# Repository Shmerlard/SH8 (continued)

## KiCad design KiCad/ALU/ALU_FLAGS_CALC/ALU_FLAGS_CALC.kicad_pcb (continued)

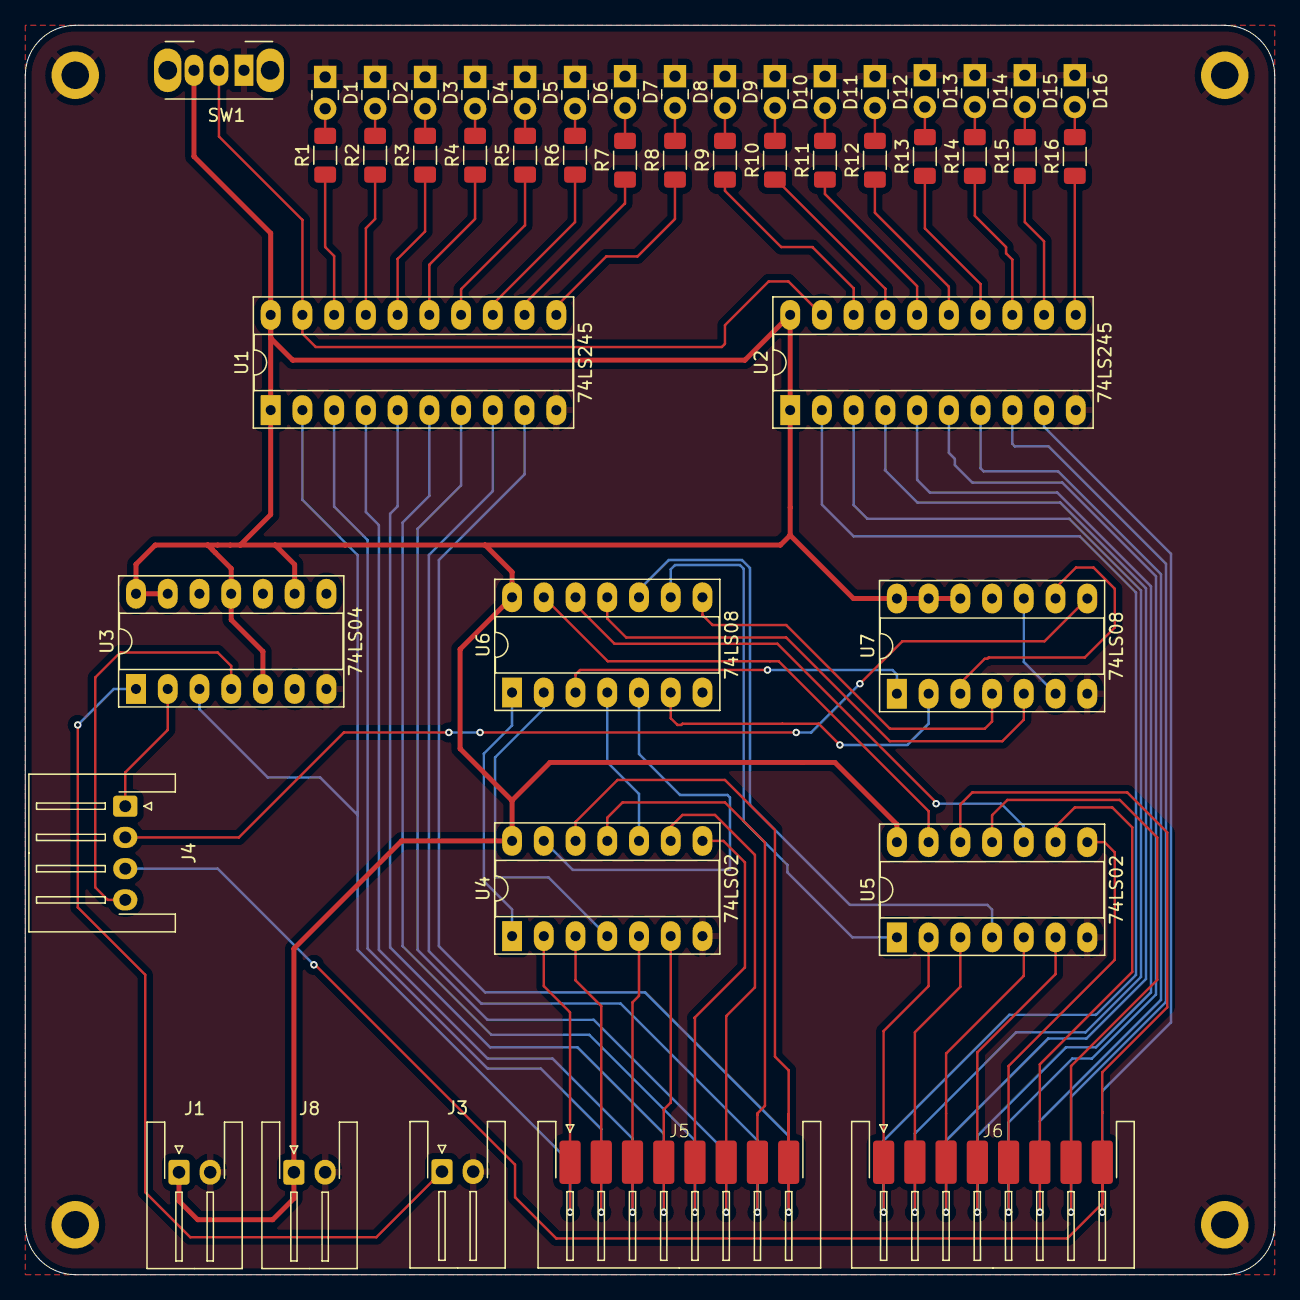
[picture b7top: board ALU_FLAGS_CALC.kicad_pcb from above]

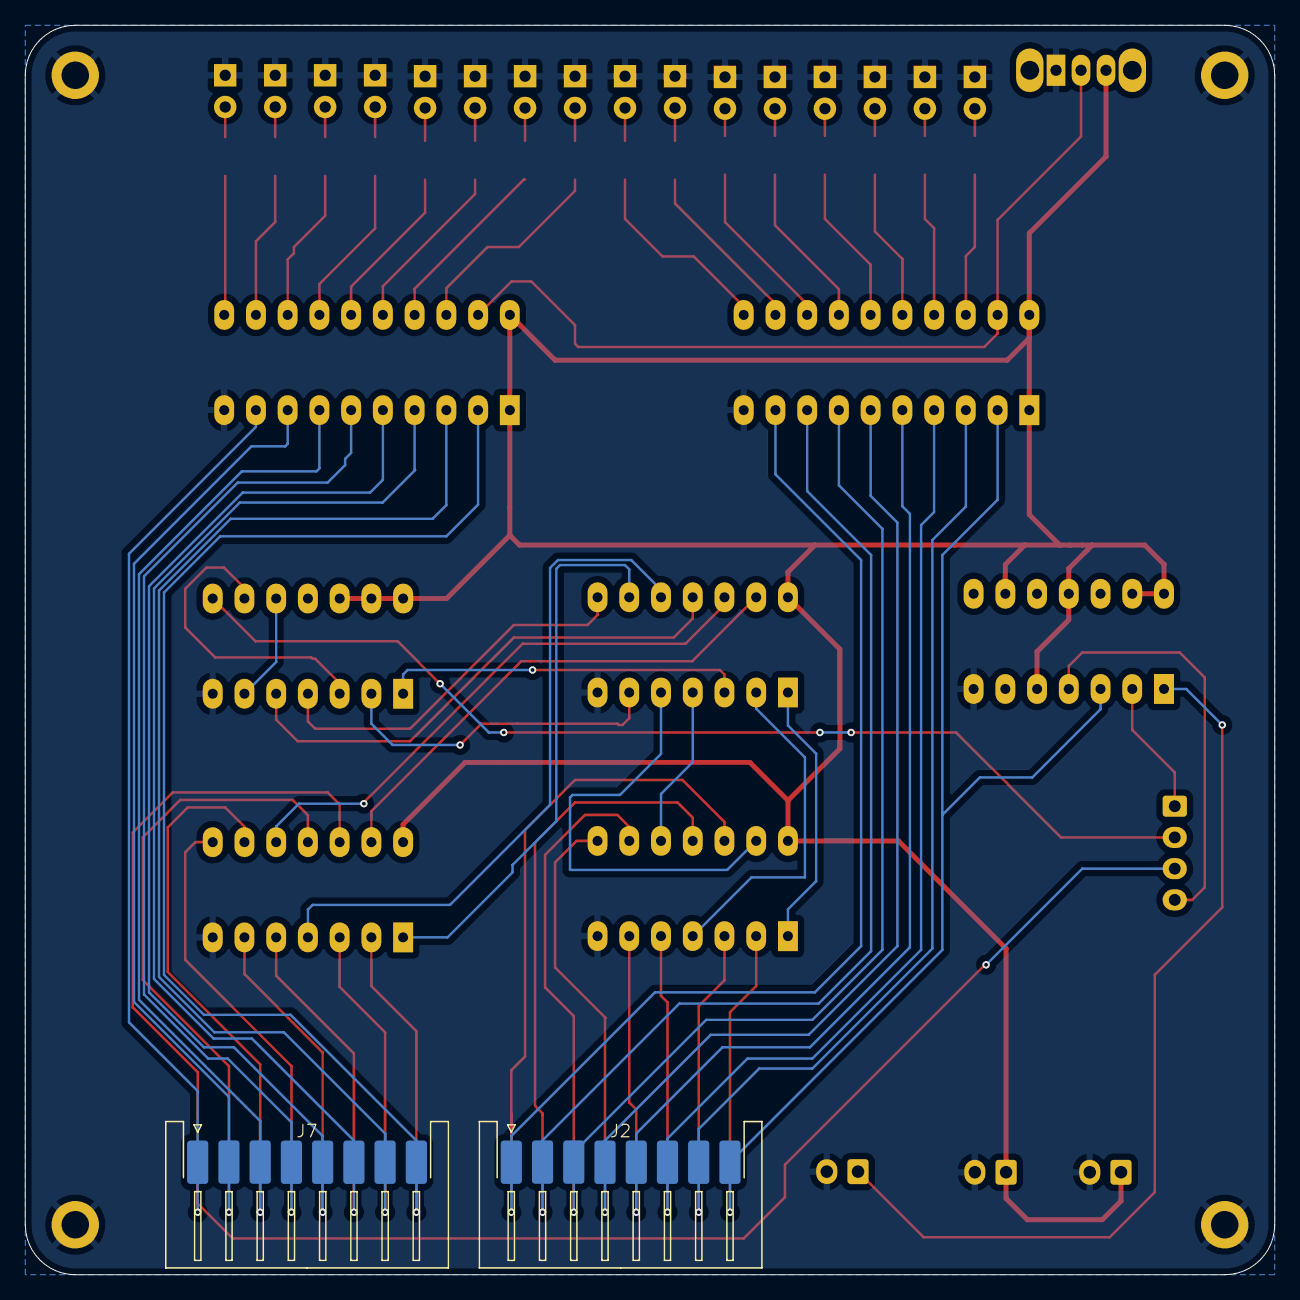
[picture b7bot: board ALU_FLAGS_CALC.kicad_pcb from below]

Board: 2 copper layers, 100.0 x 100.0 mm, 52 parts (2 on the bottom side), 69 nets.

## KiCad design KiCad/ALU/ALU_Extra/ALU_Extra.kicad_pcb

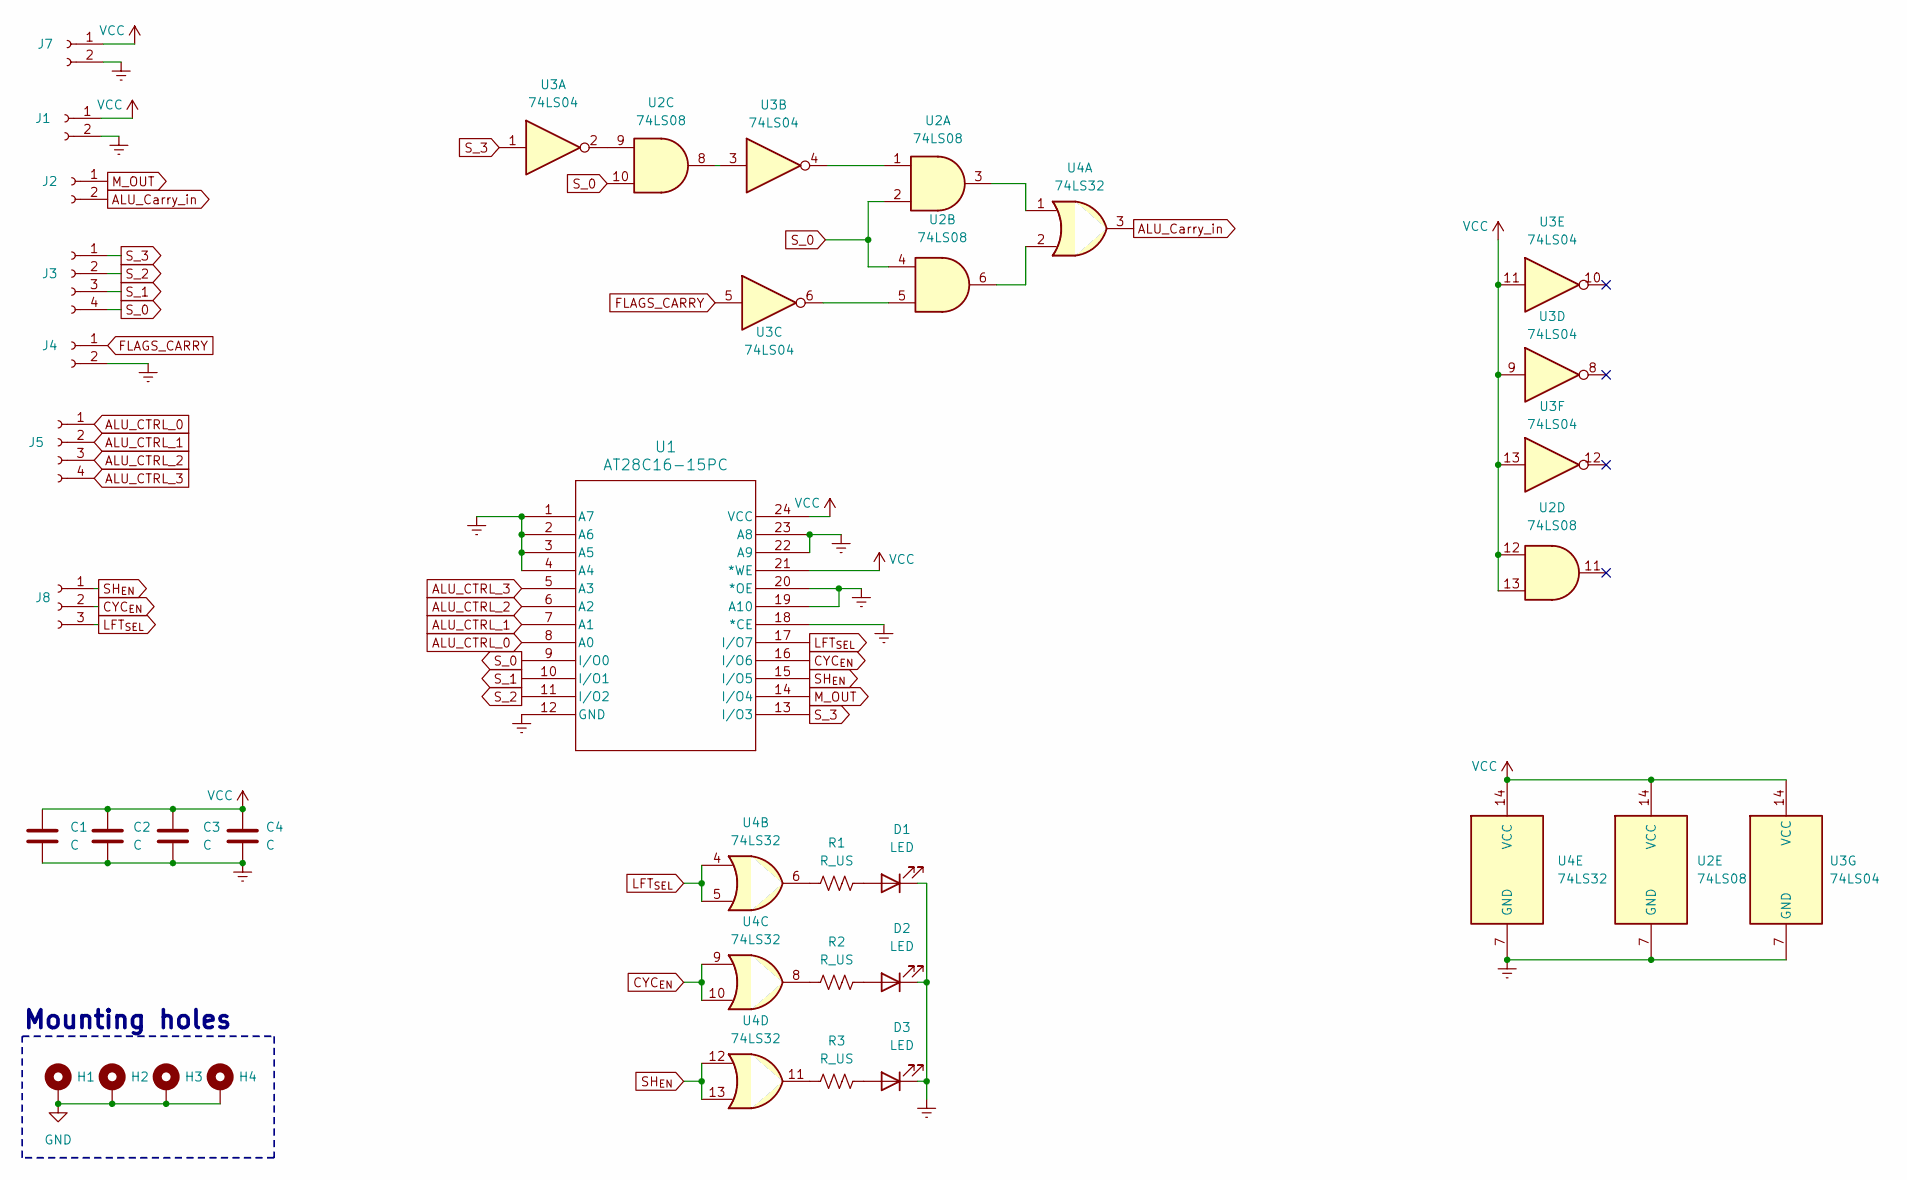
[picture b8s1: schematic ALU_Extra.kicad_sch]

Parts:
C1, C2, C3, C4: C; C_Disc_D3.8mm_W2.6mm_P2.50mm
D1, D2, D3: LED; LED_2512_6332Metric_Pad1.52x3.35mm_HandSolder
H1, H2, H3, H4: MountingHole_Pad; MountingHole_2.2mm_M2_DIN965_Pad
J1, J2, J4, J7: Conn_01x02_Socket; JST_XH_S2B-XH-A-1_1x02_P2.50mm_Horizontal
J3, J5: Conn_01x04_Socket; JST_XH_S4B-XH-A-1_1x04_P2.50mm_Horizontal
J8: Conn_01x03_Socket; JST_XH_S3B-XH-A-1_1x03_P2.50mm_Horizontal
R1, R2, R3: R_US; R_1206_3216Metric_Pad1.30x1.75mm_HandSolder
U1: AT28C16-15PC; DIP-24_W15.24mm_LongPads
U2: 74LS08; DIP-14_W7.62mm_Socket_LongPads
U3: 74LS04; DIP-14_W7.62mm_Socket_LongPads
U4: 74LS32; DIP-14_W7.62mm_Socket_LongPads

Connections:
ALU_CTRL_0: J5.1, U1.8 (A0)
ALU_CTRL_1: J5.2, U1.7 (A1)
ALU_CTRL_2: J5.3, U1.6 (A2)
ALU_CTRL_3: J5.4, U1.5 (A3)
ALU_Carry_in: J2.2, U4.3
CYC_{EN}: J8.2, U1.16 (I/O6), U4.9, U4.10
FLAGS_CARRY: J4.1, U3.5
GND: C1.2, C2.2, C3.2, C4.2, D1.1 (K), D2.1 (K), D3.1 (K), H1.1, H2.1, H3.1, H4.1, J1.2, J4.2, J7.2, U1.1 (A7), U1.2 (A6), U1.3 (A5), U1.4 (A4), U1.12 (GND), U1.18 (*CE), U1.19 (A10), U1.20 (*OE), U1.22 (A9), U1.23 (A8), U2.7 (GND), U3.7 (GND), U4.7 (GND)
LFT_{SEL}: J8.3, U1.17 (I/O7), U4.4, U4.5
M_OUT: J2.1, U1.14 (I/O4)
unnamed: D1.2 (A), R1.2
unnamed: D2.2 (A), R2.2
unnamed: D3.2 (A), R3.2
unnamed: R1.1, U4.6
unnamed: R2.1, U4.8
unnamed: R3.1, U4.11
unnamed: U2.1, U3.4
unnamed: U2.3, U4.1
unnamed: U2.5, U3.6
unnamed: U2.6, U4.2
unnamed: U2.8, U3.3
unnamed: U2.9, U3.2
SH_{EN}: J8.1, U1.15 (I/O5), U4.12, U4.13
S_0: J3.4, U1.9 (I/O0), U2.2, U2.4, U2.10
S_1: J3.3, U1.10 (I/O1)
S_2: J3.2, U1.11 (I/O2)
S_3: J3.1, U1.13 (I/O3), U3.1
VCC: C1.1, C2.1, C3.1, C4.1, J1.1, J7.1, U1.21 (*WE), U1.24 (VCC), U2.12, U2.13, U2.14 (VCC), U3.9, U3.11, U3.13, U3.14 (VCC), U4.14 (VCC)

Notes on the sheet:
Mounting holes

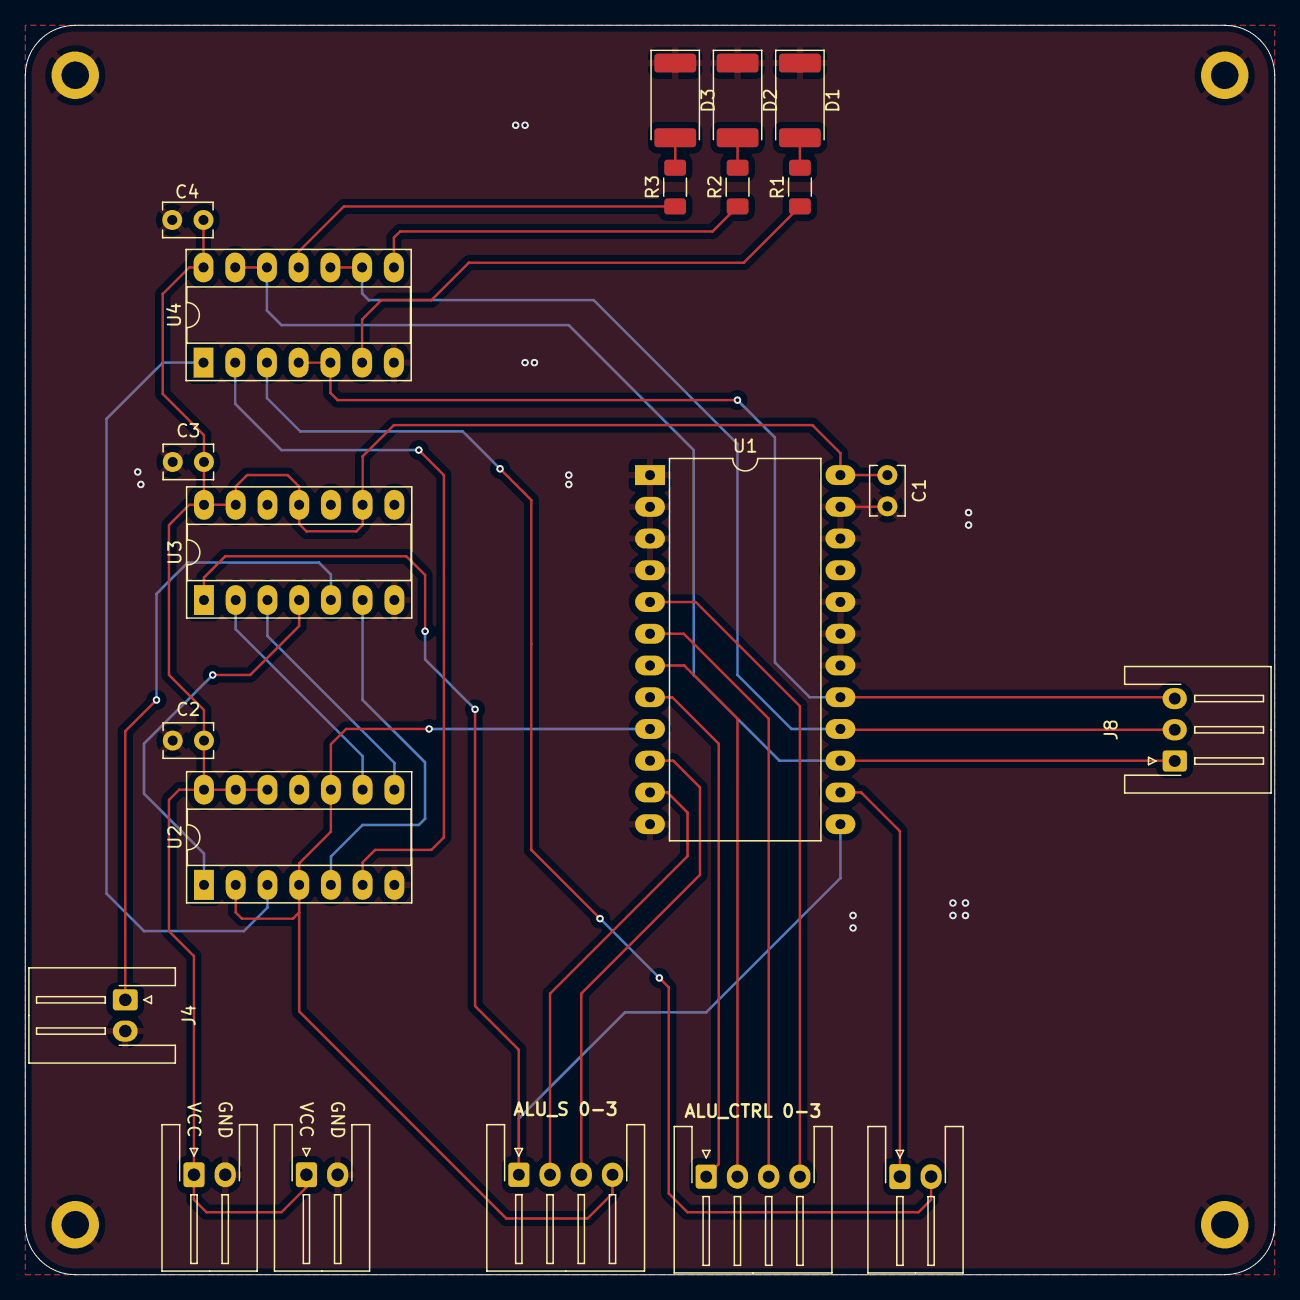
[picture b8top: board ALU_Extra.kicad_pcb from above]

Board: 2 copper layers, 100.0 x 100.0 mm, 25 parts (0 on the bottom side), 28 nets.

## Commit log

2024-06-09 added instruction set
2024-06-09 added circ and diagram
2024-06-09 updated drawing
2024-06-09 added gitignore, updated diagram
2024-06-10 add wiki
2024-06-10 added some to wiki
2024-06-10 modified diagram
    added timing and a few control lines
2024-06-10 background
2024-06-10 changed to 16bit, added logisim
2024-06-10 updated logisim and main diagram
2024-06-10 excel
2024-06-11 added data sheets, and microcode
2024-06-12 addressing modes and instruction format changed
2024-06-12 Added MR, started the assembler,
    updated the instruction format
    added problems
2024-06-13 alu
    added a working alu to logisim, including the 74xx circuit
2024-06-13 solved the alu and conditions problem
    need to reduce the control lines from the address registers to add SHC, SHA
2024-06-14 shifting is working!
2024-06-14 added a bunch of python code
    added control logic, started the program to write to the control logic
2024-06-14 added eeprom programmer
2024-06-15 fixed some python bugs
2024-06-15 rewrote the python code
2024-06-15 solved the logic problem
2024-06-15 added line to gitignore
2024-06-15 rm -r .vscode/
2024-06-15 some cleaning
2024-06-16 minor changes to readme
2024-06-16 added JMP, fixed conditions
2024-06-17 some wiki additions,
    moving to change the instruction structure and instructrure set.
2024-06-18 changed the instruction
    reduced control logic to 3 eeproms, opcode is now 4 bits, added Vout for different jmp conditions, added special addressing mode for different operations
2024-06-21 added control lines description
2024-06-21 added control lines for push, chagned order of SP++ and Ra->SP
2024-06-22 fixed carry problem, added conditional jumps
2024-06-22 fixed some directories
2024-06-22 started assembler
2024-07-01 added gallery
2024-08-15 added shr
2024-08-16 fixed alu
    changed the alu inputs, need to fix the microcode in the xlsx file, also added the alu diagram in the draw.io file
2024-08-17 alu fixed
    fixed some instructions, more to come
2024-08-18 more instruction, fixed alu
2024-08-19 added more instructions
2024-08-20 added more instruction
2024-08-20 Alternate Instruction Update
    address mode reduced from 3 bits to 2,
    added alternate mode for SHR, RRC, SUB, any possibly more
2024-08-23 chore: Update assembler to process labels and origins
2024-08-24 Assembler
    Last steps on the assembler
2024-08-25 more-assembler
2024-08-25 finished the assembler and the transition to 5bit opcode
2024-08-25 more instructions, small fix for the assembler
    now the assembler will output the file the same directory as the input file
2024-08-25 readme fix
2024-08-26 fixed some instructions, added highlight for neovim
    first try with kicad
2024-09-26 added kicad schematics and pcb's
2024-10-02 finished registier file boards
2024-10-05 added con_ctrl board mdr_mar
2024-10-16 added more boards, added pcb standarts
2024-10-19 created standarts for PCB's
